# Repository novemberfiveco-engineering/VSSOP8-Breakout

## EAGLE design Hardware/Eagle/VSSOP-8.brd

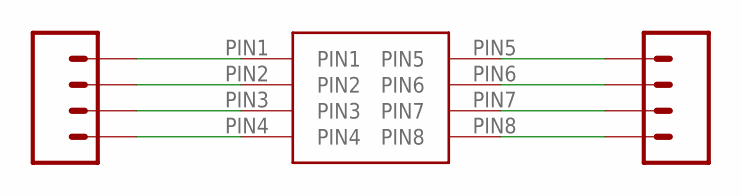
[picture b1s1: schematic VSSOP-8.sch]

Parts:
J1, J2: CONN_04; 1X04
U$1: VSSOP-8

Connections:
unnamed: J1.4, U$1.PIN1
unnamed: J1.3, U$1.PIN2
unnamed: J1.2, U$1.PIN3
unnamed: J1.1, U$1.PIN4
unnamed: J2.1, U$1.PIN5
unnamed: J2.2, U$1.PIN6
unnamed: J2.3, U$1.PIN7
unnamed: J2.4, U$1.PIN8

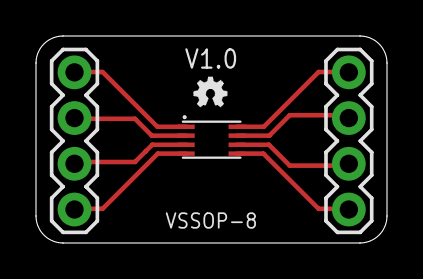
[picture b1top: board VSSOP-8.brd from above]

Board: 2 copper layers, 19.5 x 11.5 mm, 5 parts (0 on the bottom side), 8 nets.

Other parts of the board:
U$2: LOGO-OSHWA
U$3: LOGO-NOVEMERFIVE-7SCALE

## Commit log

2017-05-15 Added project library

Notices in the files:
parts and their libraries:
SparkFun-Connectors: Licensing: Creative Commons ShareAlike 4.0 International - https://creativecommons.org/licenses/by-sa/4.0
